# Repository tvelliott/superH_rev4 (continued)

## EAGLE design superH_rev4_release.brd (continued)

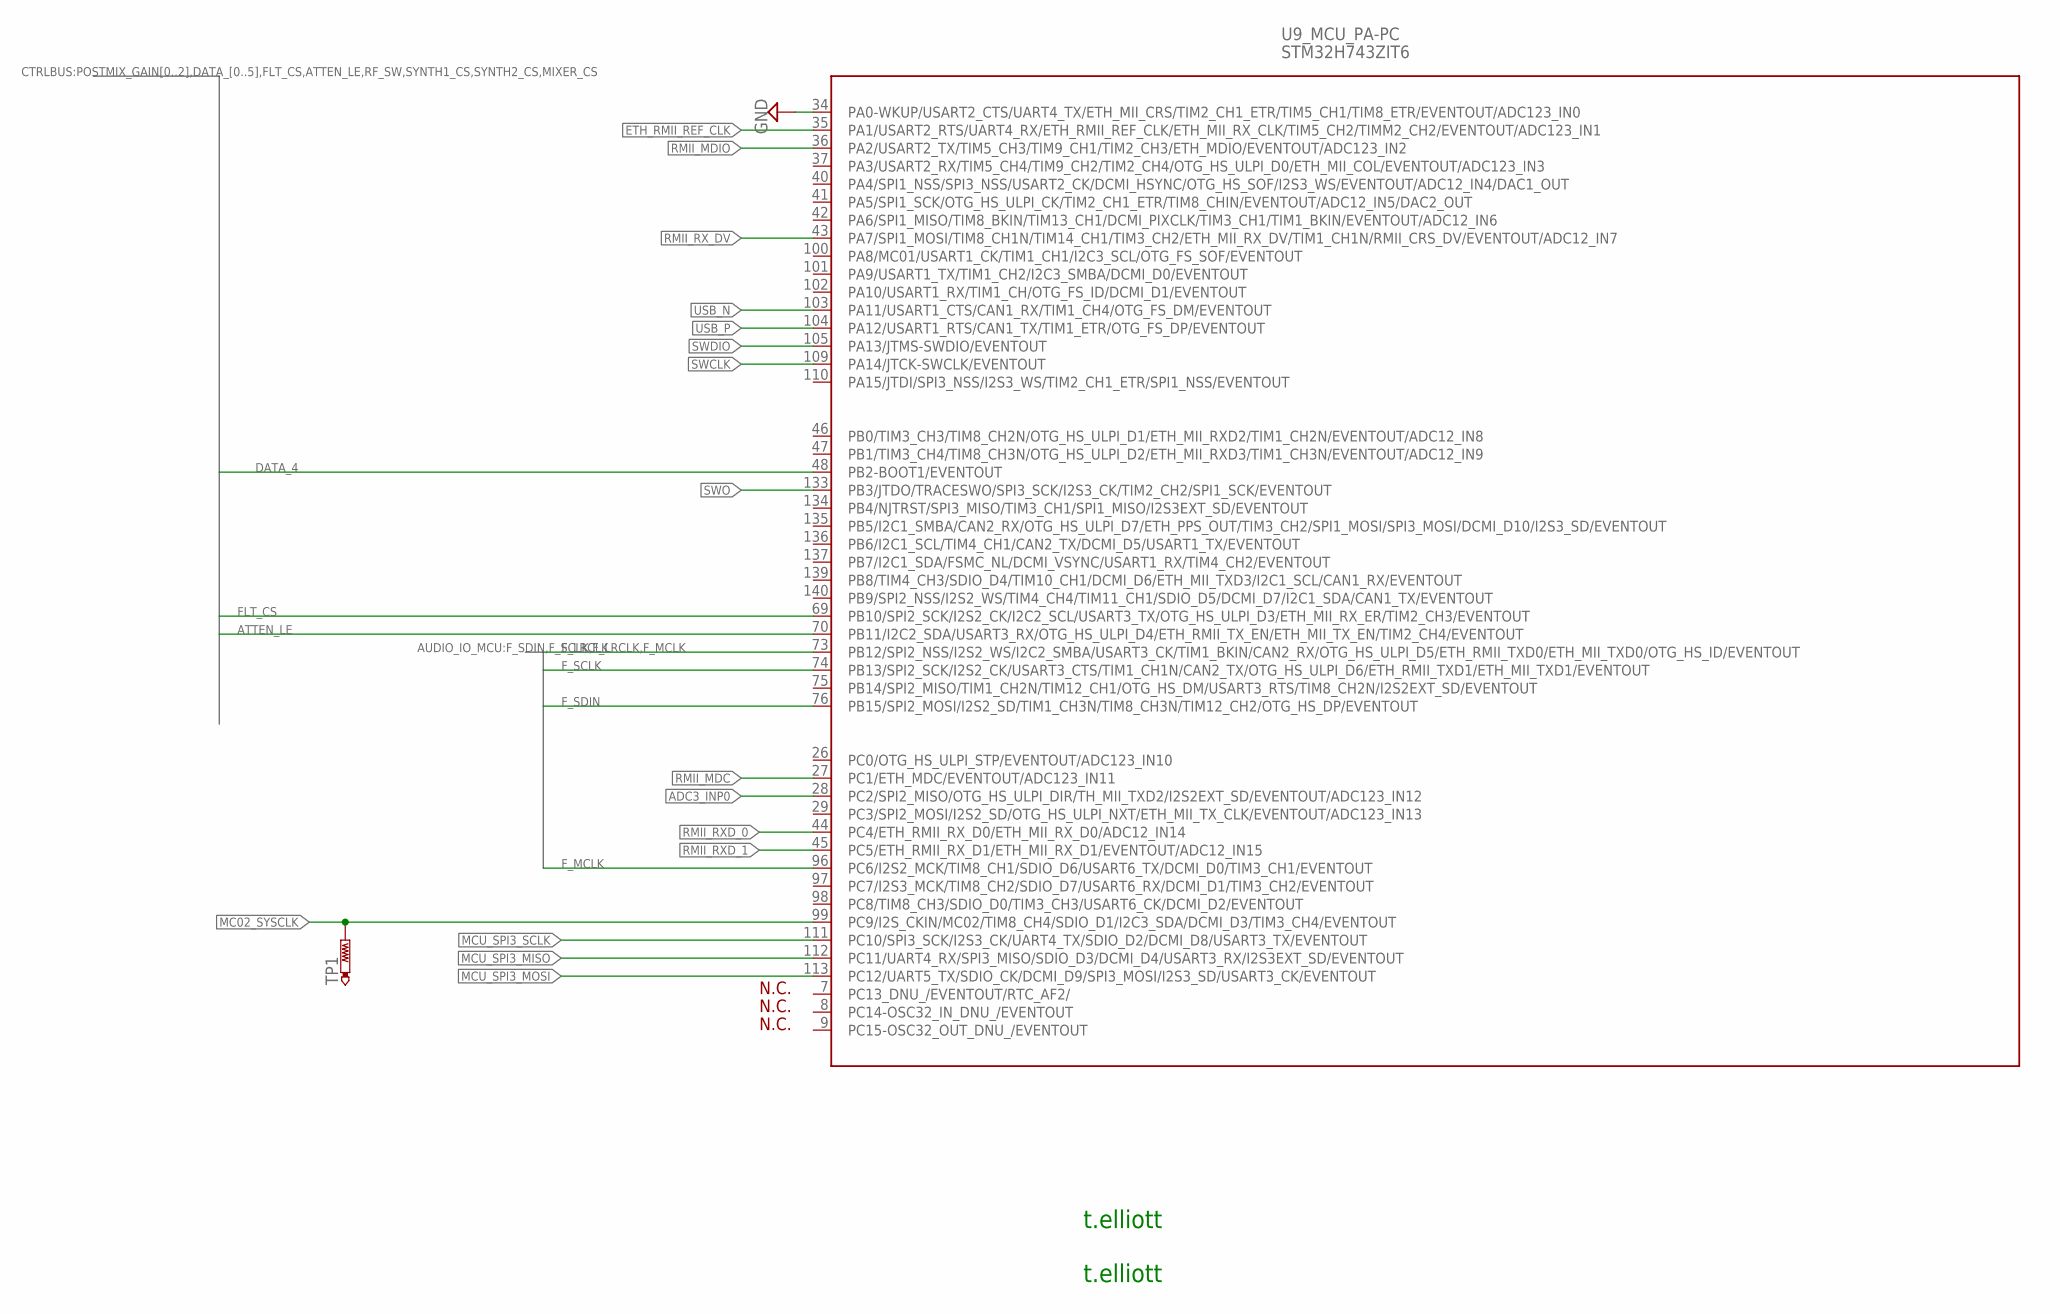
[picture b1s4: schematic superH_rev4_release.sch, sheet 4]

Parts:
TP1: PTR1TP08R; TP08R
U9: STM32H743ZIT6; STM32F407_144

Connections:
ADC3_INP0: U9.28 (PC2/SPI2_MISO/OTG_HS_ULPI_DIR/TH_MII_TX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); also elsewhere on the board
ATTEN_LE: U9.70 (PB11/I2C2_SDA/USART3_RX/OTG_HS_ULPI_D4/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); also elsewhere on the board
DATA_4: U9.48 (PB2-BOOT1/EVENTOUT); also elsewhere on the board
ETH_RMII_REF_CLK: U9.35 (PA1/USART2_RTS/UART4_RX/ETH_RMII_REF_CL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); also elsewhere on the board
FLT_CS: U9.69 (PB10/SPI2_SCK/I2S2_CK/I2C2_SCL/USART3_T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); also elsewhere on the board
F_LRCLK: U9.73 (PB12/SPI2_NSS/I2S2_WS/I2C2_SMBA/USART3_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); also elsewhere on the board
F_MCLK: U9.96 (PC6/I2S2_MCK/TIM8_CH1/SDIO_D6/USART6_TX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); also elsewhere on the board
F_SCLK: U9.74 (PB13/SPI2_SCK/I2S2_CK/USART3_CTS/TIM1_C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); also elsewhere on the board
F_SDIN: U9.76 (PB15/SPI2_MOSI/I2S2_SD/TIM1_CH3N/TIM8_C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); also elsewhere on the board
GND: U9.34 (PA0-WKUP/USART2_CTS/UART4_TX/ETH_MII_CR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); also elsewhere on the board
MC02_SYSCLK: TP1.TP, U9.99 (PC9/I2S_CKIN/MC02/TIM8_CH4/SDIO_D1/I2C3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)
MCU_SPI3_MISO: U9.112 (PC11/UART4_RX/SPI3_MISO/SDIO_D3/DCMI_D4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); also elsewhere on the board
MCU_SPI3_MOSI: U9.113 (PC12/UART5_TX/SDIO_CK/DCMI_D9/SPI3_MOSI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); also elsewhere on the board
MCU_SPI3_SCLK: U9.111 (PC10/SPI3_SCK/I2S3_CK/UART4_TX/SDIO_D2/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); also elsewhere on the board
RMII_MDC: U9.27 (PC1/ETH_MDC/EVENTOUT/ADC123_IN11); also elsewhere on the board
RMII_MDIO: U9.36 (PA2/USART2_TX/TIM5_CH3/TIM9_CH1/TIM2_CH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); also elsewhere on the board
RMII_RXD_0: U9.44 (PC4/ETH_RMII_RX_D0/ETH_MII_RX_D0/ADC12_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); also elsewhere on the board
RMII_RXD_1: U9.45 (PC5/ETH_RMII_RX_D1/ETH_MII_RX_D1/EVENTO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); also elsewhere on the board
RMII_RX_DV: U9.43 (PA7/SPI1_MOSI/TIM8_CH1N/TIM14_CH1/TIM3_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); also elsewhere on the board
SWCLK: U9.109 (PA14/JTCK-SWCLK/EVENTOUT); also elsewhere on the board
SWDIO: U9.105 (PA13/JTMS-SWDIO/EVENTOUT); also elsewhere on the board
SWO: U9.133 (PB3/JTDO/TRACESWO/SPI3_SCK/I2S3_CK/TIM2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); also elsewhere on the board
USB_N: U9.103 (PA11/USART1_CTS/CAN1_RX/TIM1_CH4/OTG_FS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); also elsewhere on the board
USB_P: U9.104 (PA12/USART1_RTS/CAN1_TX/TIM1_ETR/OTG_FS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); also elsewhere on the board

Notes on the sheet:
t.elliott

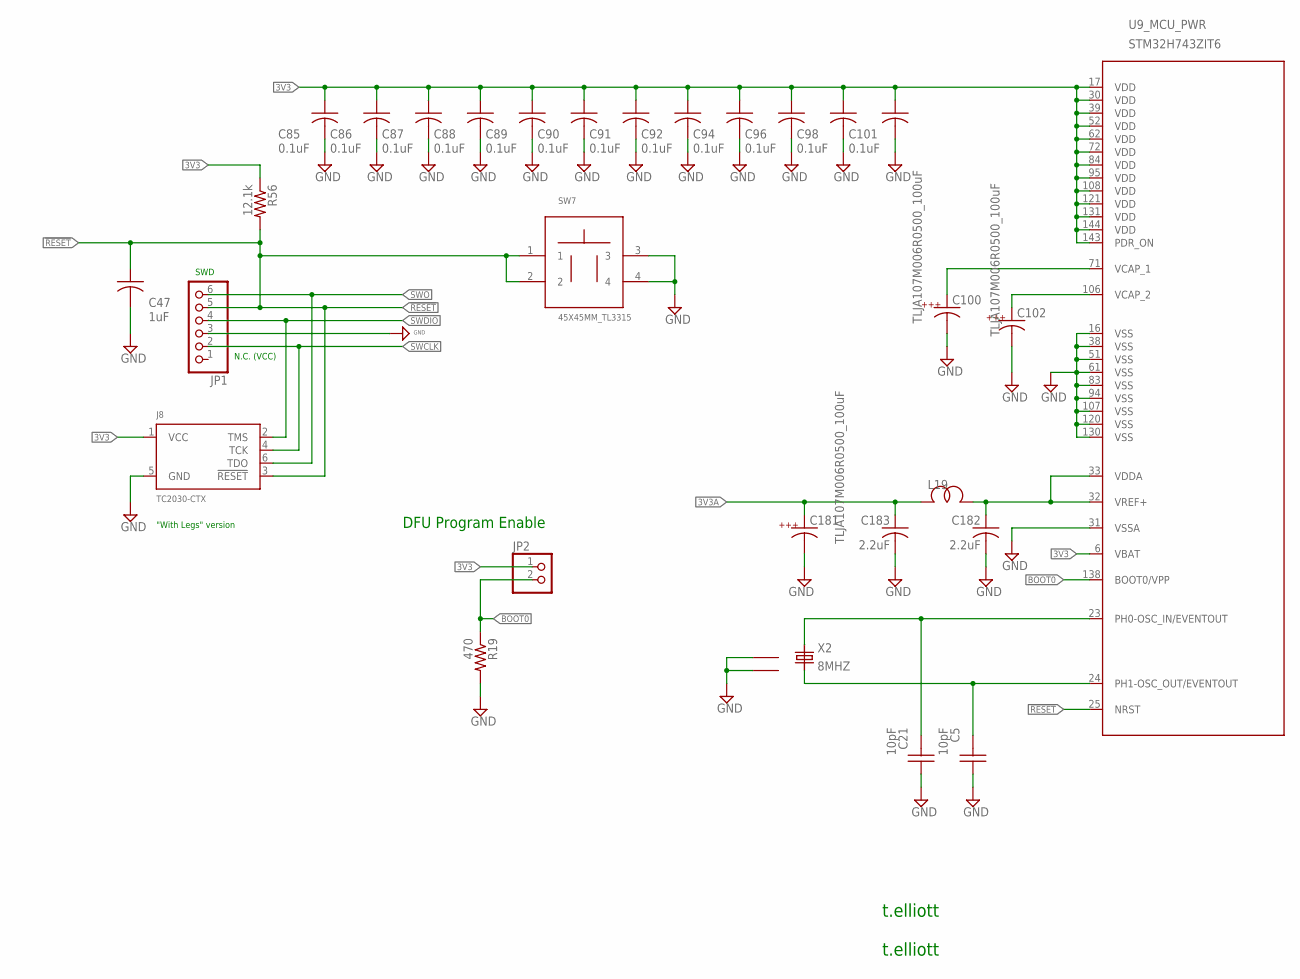
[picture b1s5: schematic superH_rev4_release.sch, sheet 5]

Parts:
C5, C21: 10pF; C0402
C47: 1uF; 0402
C85, C86, C87, C88, C89, C90, C91, C92, C94, C96, C98, C101: 0.1uF; 0402
C100, C102, C181: TLJA107M006R0500_100uF; 1210K
C182, C183: 2.2uF; C0805
J8: TC2030-CTX; TC2030-IDC
JP1: PINHD-1X6; 1X06
JP2: PINHD-1X2; 1X02
L19: WE-CBF_0603; 0603
R19: 470; R0402
R56: 12.1k; R0603
SW7: 45X45MM_TL3315; PBUT_SW_TACTILE_4_5MMX4_5MM
U9: STM32H743ZIT6; STM32F407_144
X2: 8MHZ; ECS-250-20-30B-DU_CRYSTAL

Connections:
3V3: C85.1 (A), C86.1 (A), C87.1 (A), C88.1 (A), C89.1 (A), C90.1 (A), C91.1 (A), C92.1 (A), C94.1 (A), C96.1 (A), C98.1 (A), C101.1 (A), J8.1 (VCC), JP2.1, R56.1, U9.6 (VBAT), U9.17 (VDD), U9.30 (VDD), U9.39 (VDD), U9.52 (VDD), U9.62 (VDD), U9.72 (VDD), U9.84 (VDD), U9.95 (VDD), U9.108 (VDD), U9.121 (VDD), U9.131 (VDD), U9.143 (PDR_ON), U9.144 (VDD); also elsewhere on the board
3V3A: C181.A, C183.1, L19.1; also elsewhere on the board
20MHZ_REF: C21.2, U9.23 (PH0-OSC_IN/EVENTOUT), X2.1
!RESET: C47.1 (A), J8.3 (!RESET), JP1.5, R56.2, SW7.1, SW7.2, U9.25 (NRST); also elsewhere on the board
BOOT0: JP2.2, R19.1, U9.138 (BOOT0/VPP)
GND: C5.1, C21.1, C47.2 (C), C85.2 (C), C86.2 (C), C87.2 (C), C88.2 (C), C89.2 (C), C90.2 (C), C91.2 (C), C92.2 (C), C94.2 (C), C96.2 (C), C98.2 (C), C100.C, C101.2 (C), C102.C, C181.C, C182.2, C183.2, J8.5 (GND), JP1.3, R19.2, SW7.3, SW7.4, U9.16 (VSS), U9.31 (VSSA), U9.38 (VSS), U9.51 (VSS), U9.61 (VSS), U9.83 (VSS), U9.94 (VSS), U9.107 (VSS), U9.120 (VSS), U9.130 (VSS), X2.GND@1 (1), X2.GND@2 (2); also elsewhere on the board
unnamed: C182.1, L19.2, U9.32 (VREF+), U9.33 (VDDA)
unnamed: C102.A, U9.106 (VCAP_2)
unnamed: C100.A, U9.71 (VCAP_1)
SWCLK: J8.4 (TCK), JP1.2; also elsewhere on the board
SWDIO: J8.2 (TMS), JP1.4; also elsewhere on the board
SWO: J8.6 (TDO), JP1.6; also elsewhere on the board
X2: C5.2, U9.24 (PH1-OSC_OUT/EVENTOUT), X2.3

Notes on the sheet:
t.elliott
SWD
N.C. (VCC)
"With Legs" version
DFU Program Enable

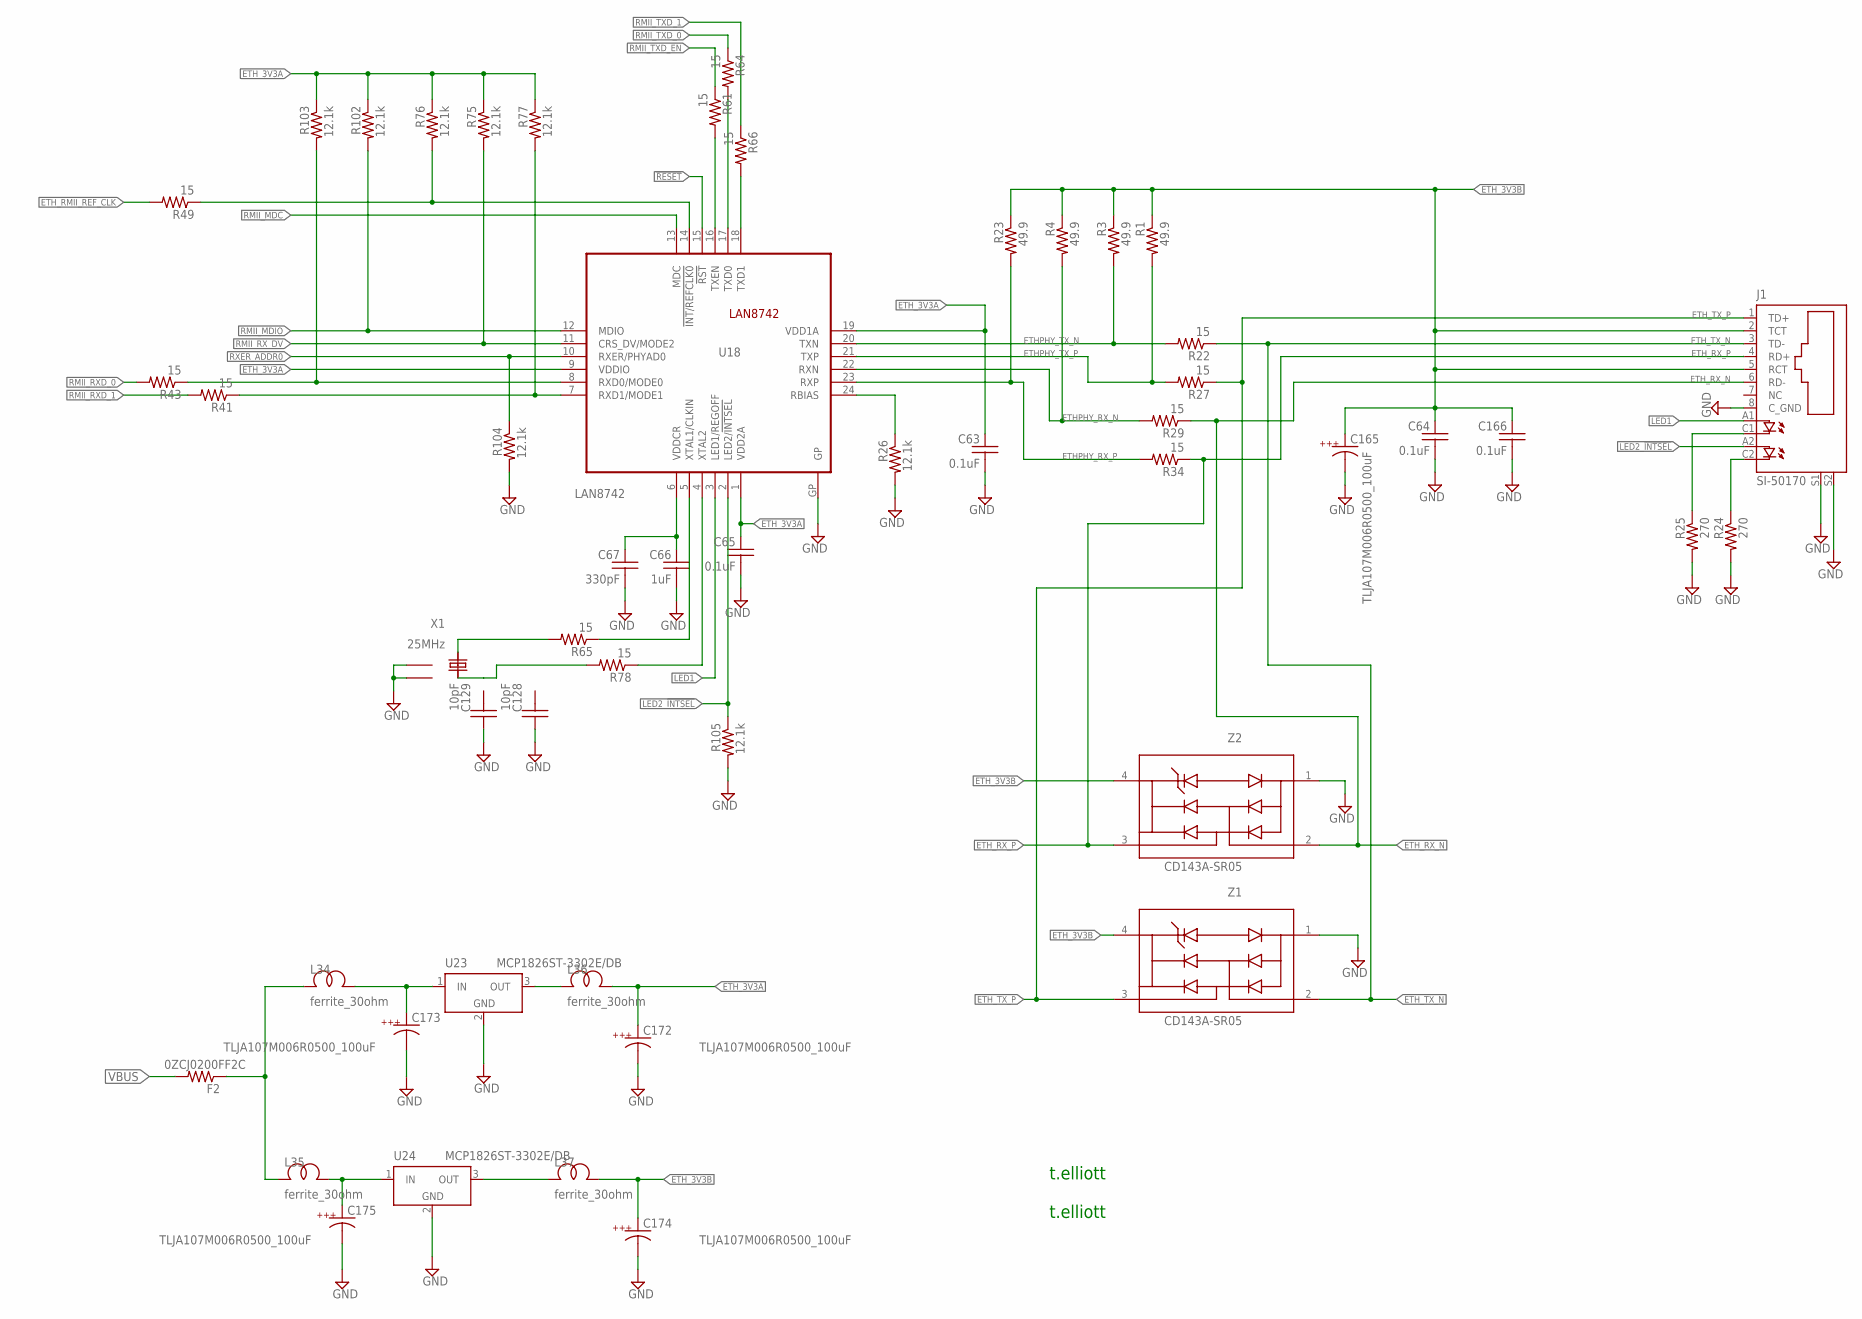
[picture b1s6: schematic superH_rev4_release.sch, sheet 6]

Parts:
C63, C64, C65, C166: 0.1uF; C0603
C66: 1uF; C0603
C67: 330pF; C0603
C128, C129: 10pF; C0402
C165, C172, C173, C174, C175: TLJA107M006R0500_100uF; 1210K
F2: 0ZCJ0200FF2C; R1206
J1: SI-50170
L34, L35, L36, L37: ferrite_30ohm; 0603
R1, R3, R4, R23: 49.9; R0603
R22, R27, R29, R34, R41, R43, R49, R61, R64, R65, R66, R78: 15; R0402
R24, R25: 270; R0603
R26, R75, R76, R77, R102, R103, R104, R105: 12.1k; R0603
U18: LAN8742; QFN-24
U23, U24: MCP1826ST-3302E/DB; SOT223
X1: 25MHz; ECS-250-20-30B-DU_CRYSTAL
Z1, Z2: CD143A-SR05; SR2.8.TCT_1PRIMARY

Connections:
!RESET: U18.15 (!RST); also elsewhere on the board
ETHPHY_RX_N: R4.2, R29.2, U18.22 (RXN)
ETHPHY_RX_P: R23.2, R34.2, U18.23 (RXP)
ETHPHY_TX_N: R3.2, R22.2, U18.20 (TXN)
ETHPHY_TX_P: R1.2, R27.2, U18.21 (TXP)
ETH_3V3A: C63.1, C65.1, C172.A, L36.2, R75.1, R76.1, R77.1, R102.1, R103.1, U18.1 (VDD2A), U18.9 (VDDIO), U18.19 (VDD1A)
ETH_3V3B: C64.1, C165.A, C166.1, C174.A, J1.2 (TCT), J1.5 (RCT), L37.2, R1.1, R3.1, R4.1, R23.1, Z1.4 (REF), Z2.4 (REF)
ETH_RMII_REF_CLK: R49.2; also elsewhere on the board
ETH_RX_N: J1.6 (RD-), R29.1, Z2.2 (I/O)
ETH_RX_P: J1.4 (RD+), R34.1, Z2.3 (I/O)
ETH_TX_N: J1.3 (TD-), R22.1, Z1.2 (I/O)
ETH_TX_P: J1.1 (TD+), R27.1, Z1.3 (I/O)
ETH_VIN: F2.1, L34.1, L35.1
GND: C63.2, C64.2, C65.2, C66.2, C67.2, C128.1, C129.1, C165.C, C166.2, C172.C, C173.C, C174.C, C175.C, J1.8 (C_GND), J1.S1, J1.S2, R24.2, R25.2, R26.2, R104.2, R105.2, U18.GP, U23.2 (GND), U23.4 (GND), U24.2 (GND), U24.4 (GND), X1.GND@1 (1), X1.GND@2 (2), Z1.1 (GND), Z2.1 (GND); also elsewhere on the board
LED1: J1.A1 (A), U18.3 (LED1/REGOFF)
LED2_!INTSEL: J1.A2 (A1), R105.1, U18.2 (LED2/!INTSEL)
unnamed: C173.A, L34.2, U23.1 (IN)
unnamed: R26.1, U18.24 (RBIAS)
unnamed: C66.1, C67.1, U18.6 (VDDCR)
unnamed: J1.C2 (C1), R24.1
unnamed: J1.C1 (C), R25.1
unnamed: R78.1, U18.4 (XTAL2)
unnamed: R65.1, U18.5 (XTAL1/CLKIN)
unnamed: C175.A, L35.2, U24.1 (IN)
unnamed: L37.1, U24.3 (OUT)
unnamed: L36.1, U23.3 (OUT)
unnamed: R78.2, X1.3
unnamed: R65.2, X1.1
REF_CLK: R49.1, R76.2, U18.14 (!INT/REFCLK0)
RMII_MDC: U18.13 (MDC); also elsewhere on the board
RMII_MDIO: R102.2, U18.12 (MDIO); also elsewhere on the board
RMII_RXD_0: R43.2; also elsewhere on the board
RMII_RXD_1: R41.2; also elsewhere on the board
RMII_RX_DV: R75.2, U18.11 (CRS_DV/MODE2); also elsewhere on the board
RMII_TXD_0: R64.1; also elsewhere on the board
RMII_TXD_1: R66.1; also elsewhere on the board
RMII_TXD_EN: R61.1; also elsewhere on the board
RXD0: R43.1, R103.2, U18.8 (RXD0/MODE0)
RXD1: R41.1, R77.2, U18.7 (RXD1/MODE1)
RXER_ADDR0: R104.1, U18.10 (RXER/PHYAD0)
TXD0: R64.2, U18.17 (TXD0)
TXD1: R66.2, U18.18 (TXD1)
TXEN: R61.2, U18.16 (TXEN)
VBUS: F2.2; also elsewhere on the board

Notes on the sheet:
t.elliott

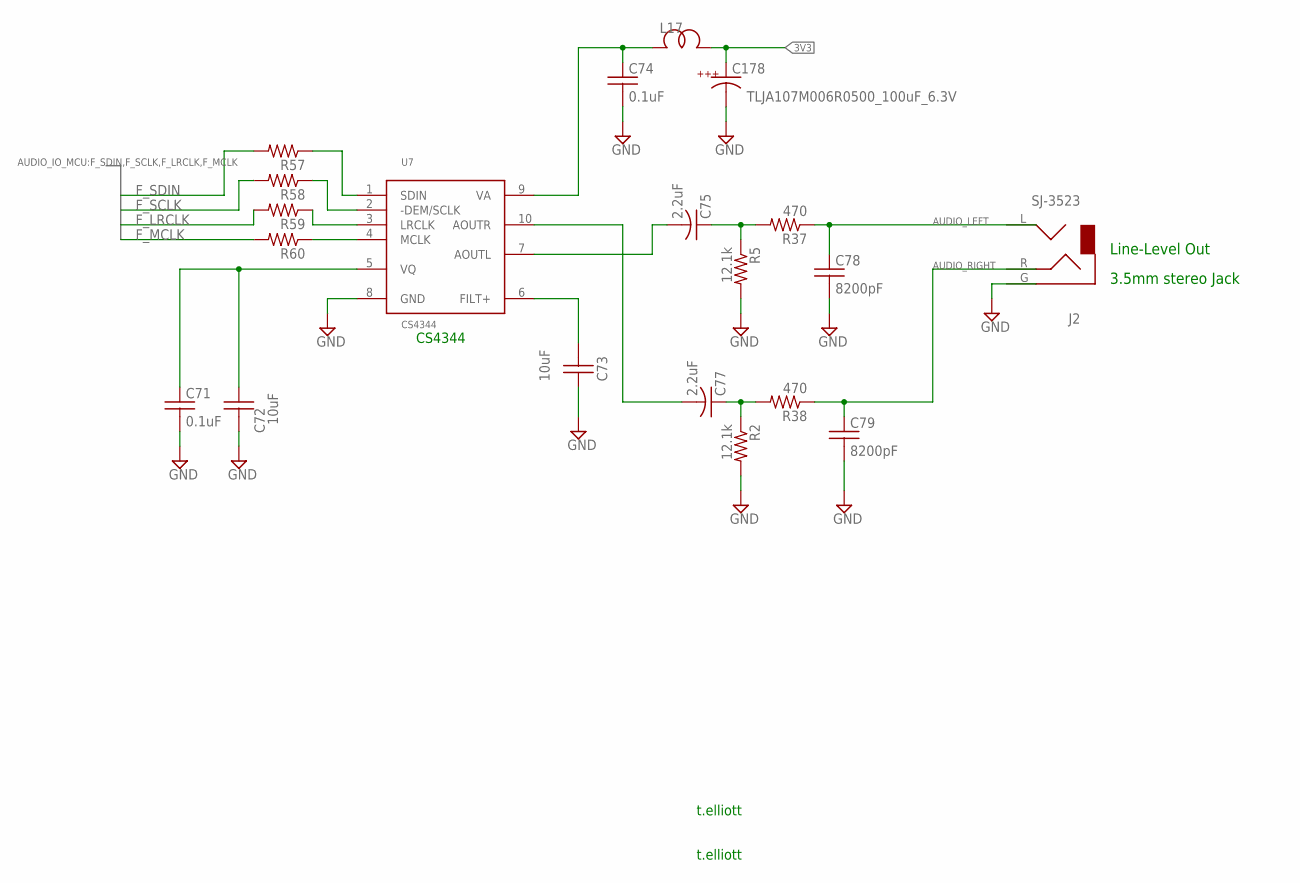
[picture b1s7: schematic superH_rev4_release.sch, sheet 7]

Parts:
C71, C74: 0.1uF; C0603
C72, C73: 10uF; C0805
C75, C77: 2.2uF; C0805
C78, C79: 8200pF; C0603
C178: TLJA107M006R0500_100uF_6.3V; 1210K
J2: SJ-3523
L17: WE-CBF_0603; 0603
R2, R5: 12.1k; R0603
R37, R38, R57, R58, R59, R60: 470; R0402
U7: CS4344; MSOP10

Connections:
3V3: C178.A, L17.2; also elsewhere on the board
AUDIO_LEFT: C79.1, J2.R, R38.1
AUDIO_RIGHT: C78.1, J2.L, R37.1
F_LRCLK: R59.2; also elsewhere on the board
F_MCLK: R60.2; also elsewhere on the board
F_SCLK: R58.2; also elsewhere on the board
F_SDIN: R57.2; also elsewhere on the board
GND: C71.2, C72.2, C73.1, C74.2, C78.2, C79.2, C178.C, J2.G, R2.2, R5.2, U7.8 (GND); also elsewhere on the board
unnamed: C77.2, U7.10 (AOUTR)
unnamed: R60.1, U7.4 (MCLK)
unnamed: R59.1, U7.3 (LRCLK)
unnamed: R58.1, U7.2 (-DEM/SCLK)
unnamed: R57.1, U7.1 (SDIN)
unnamed: C73.2, U7.6 (FILT+)
unnamed: C71.1, C72.1, U7.5 (VQ)
unnamed: C75.2, U7.7 (AOUTL)
unnamed: C75.1, R5.1, R37.2
unnamed: C77.1, R2.1, R38.2
unnamed: C74.1, L17.1, U7.9 (VA)

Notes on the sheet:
t.elliott
CS4344
Line-Level Out
3.5mm stereo Jack

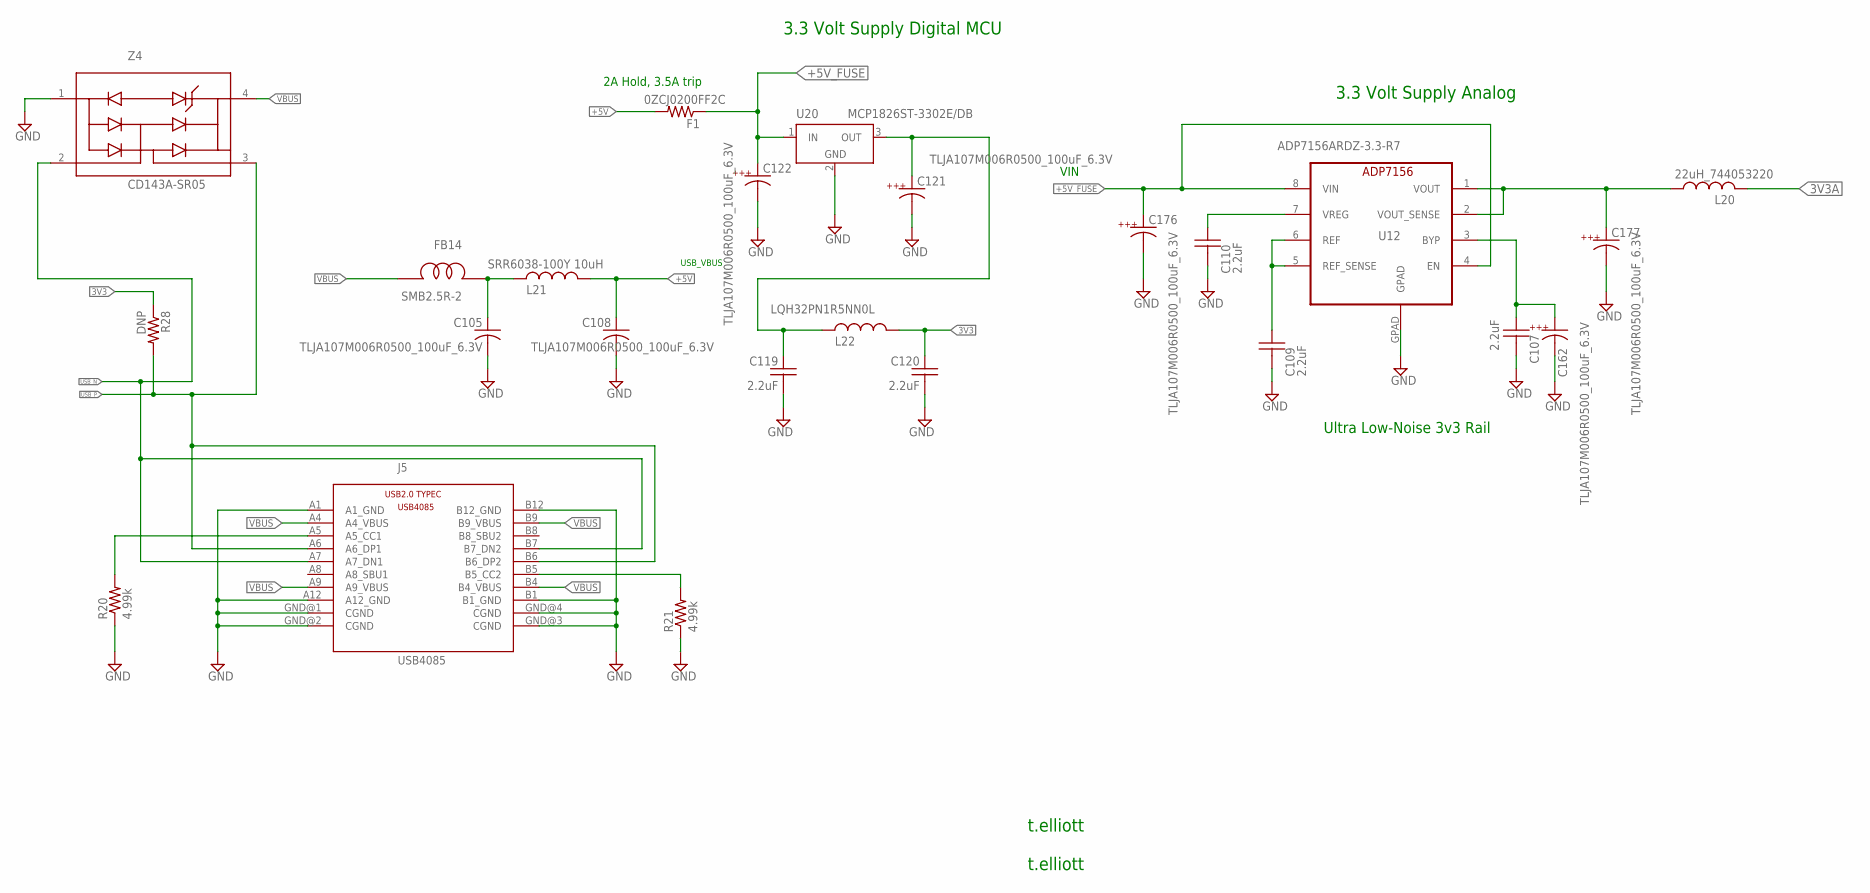
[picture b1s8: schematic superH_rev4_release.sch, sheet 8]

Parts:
C105, C108, C121, C122, C162, C176, C177: TLJA107M006R0500_100uF_6.3V; 1210K
C107, C109, C110: 2.2uF; C0805
C119, C120: 2.2uF; C0603
F1: 0ZCJ0200FF2C; R1206
FB14: SMB2.5R-2; SMB2.5-2
J5: USB4085; GCT_PN_USB4085
L20: 22uH_744053220; POWER-CHOKE_WE-TPC
L21: SRR6038-100Y 10uH; POWER-CHOKE_WE-TPC
L22: LQH32PN1R5NN0L; L3225M; PARTNUMBER ELJ-PA331KF
R20, R21: 4.99k; R0402
R28: DNP; R0603
U12: ADP7156ARDZ-3.3-R7; SO8
U20: MCP1826ST-3302E/DB; SOT223
Z4: CD143A-SR05; SR2.8.TCT_1PRIMARY

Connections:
3V3: C120.1, L22.1, R28.1; also elsewhere on the board
3V3A: L20.2; also elsewhere on the board
3V3_VIN: C119.1, C121.A, L22.2, U20.3 (OUT)
+5V: C108.A, F1.2, L21.1
+5V_FUSE: C122.A, C176.A, F1.1, U12.4 (EN), U12.8 (VIN), U20.1 (IN); also elsewhere on the board
GND: C105.C, C107.2, C108.C, C109.2, C110.2, C119.2, C120.2, C121.C, C122.C, C162.C, C176.C, C177.C, J5.A1 (A1_GND), J5.A12 (A12_GND), J5.B1 (B1_GND), J5.B12 (B12_GND), J5.GND@1 (CGND), J5.GND@2 (CGND), J5.GND@3 (CGND), J5.GND@4 (CGND), R20.1, R21.1, U12.GPAD, U20.2 (GND), U20.4 (GND), Z4.1 (GND); also elsewhere on the board
unnamed: J5.B5 (B5_CC2), R21.2
unnamed: C177.A, L20.1, U12.1 (VOUT), U12.2 (VOUT_SENSE)
unnamed: C109.1, U12.5 (REF_SENSE), U12.6 (REF)
unnamed: C110.1, U12.7 (VREG)
unnamed: C107.1, C162.A, U12.3 (BYP)
unnamed: C105.A, FB14.P$2, L21.2
unnamed: J5.A5 (A5_CC1), R20.2
USB_N: J5.A7 (A7_DN1), J5.B7 (B7_DN2), Z4.2 (I/O); also elsewhere on the board
USB_P: J5.A6 (A6_DP1), J5.B6 (B6_DP2), R28.2, Z4.3 (I/O); also elsewhere on the board
VBUS: FB14.P$1, J5.A4 (A4_VBUS), J5.A9 (A9_VBUS), J5.B4 (B4_VBUS), J5.B9 (B9_VBUS), Z4.4 (REF); also elsewhere on the board

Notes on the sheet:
t.elliott
VIN
3.3 Volt Supply Digital MCU
USB_VBUS
Ultra Low-Noise 3v3 Rail
2A Hold, 3.5A trip
3.3 Volt Supply Analog

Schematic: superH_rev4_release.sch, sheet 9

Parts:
FAB1, FAB2, FAB3, FAB4, FAB5, FAB6: 2118724; RF_SHIELD
FID1, FID2, FID3, FID4: FIDUCIALSMD; FIDUCIAL
H1, H2, H3, H4, H5, H6: MOUNT-PAD-ROUND2.8; 2,8-PAD

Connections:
GND: FAB1.P$1, FAB1.P$2, FAB1.P$3, FAB1.P$4, FAB1.P$5, FAB1.P$6, FAB1.P$7, FAB1.P$8, FAB1.P$9, FAB1.P$10, FAB1.P$11, FAB1.P$12, FAB1.P$13, FAB1.P$14, FAB1.P$15, FAB1.P$16, FAB1.P$17, FAB1.P$18, FAB1.P$19, FAB1.P$20, FAB1.P$21, FAB1.P$22, FAB1.P$23, FAB1.P$24, FAB2.P$1, FAB2.P$2, FAB2.P$3, FAB2.P$4, FAB2.P$5, FAB2.P$6, FAB2.P$7, FAB2.P$8, FAB2.P$9, FAB2.P$10, FAB2.P$11, FAB2.P$12, FAB2.P$13, FAB2.P$14, FAB2.P$15, FAB2.P$16, FAB2.P$17, FAB2.P$18, FAB2.P$19, FAB2.P$20, FAB2.P$21, FAB2.P$22, FAB2.P$23, FAB2.P$24, FAB3.P$1, FAB3.P$2, FAB3.P$3, FAB3.P$4, FAB3.P$5, FAB3.P$6, FAB3.P$7, FAB3.P$8, FAB3.P$9, FAB3.P$10, FAB3.P$11, FAB3.P$12, FAB3.P$13, FAB3.P$14, FAB3.P$15, FAB3.P$16, FAB3.P$17, FAB3.P$18, FAB3.P$19, FAB3.P$20, FAB3.P$21, FAB3.P$22, FAB3.P$23, FAB3.P$24, FAB4.P$1, FAB4.P$2, FAB4.P$3, FAB4.P$4, FAB4.P$5, FAB4.P$6, FAB4.P$7, FAB4.P$8, FAB4.P$9, FAB4.P$10, FAB4.P$11, FAB4.P$12, FAB4.P$13, FAB4.P$14, FAB4.P$15, FAB4.P$16, FAB4.P$17, FAB4.P$18, FAB4.P$19, FAB4.P$20, FAB4.P$21, FAB4.P$22, FAB4.P$23, FAB4.P$24, FAB5.P$1, FAB5.P$2, FAB5.P$3, FAB5.P$4, FAB5.P$5, FAB5.P$6, FAB5.P$7, FAB5.P$8, FAB5.P$9, FAB5.P$10, FAB5.P$11, FAB5.P$12, FAB5.P$13, FAB5.P$14, FAB5.P$15, FAB5.P$16, FAB5.P$17, FAB5.P$18, FAB5.P$19, FAB5.P$20, FAB5.P$21, FAB5.P$22, FAB5.P$23, FAB5.P$24, FAB6.P$1, FAB6.P$2, FAB6.P$3, FAB6.P$4, FAB6.P$5, FAB6.P$6, FAB6.P$7, FAB6.P$8, FAB6.P$9, FAB6.P$10, FAB6.P$11, FAB6.P$12, FAB6.P$13, FAB6.P$14, FAB6.P$15, FAB6.P$16, FAB6.P$17, FAB6.P$18, FAB6.P$19, FAB6.P$20, FAB6.P$21, FAB6.P$22, FAB6.P$23, FAB6.P$24; also elsewhere on the board

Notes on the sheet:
t.elliott

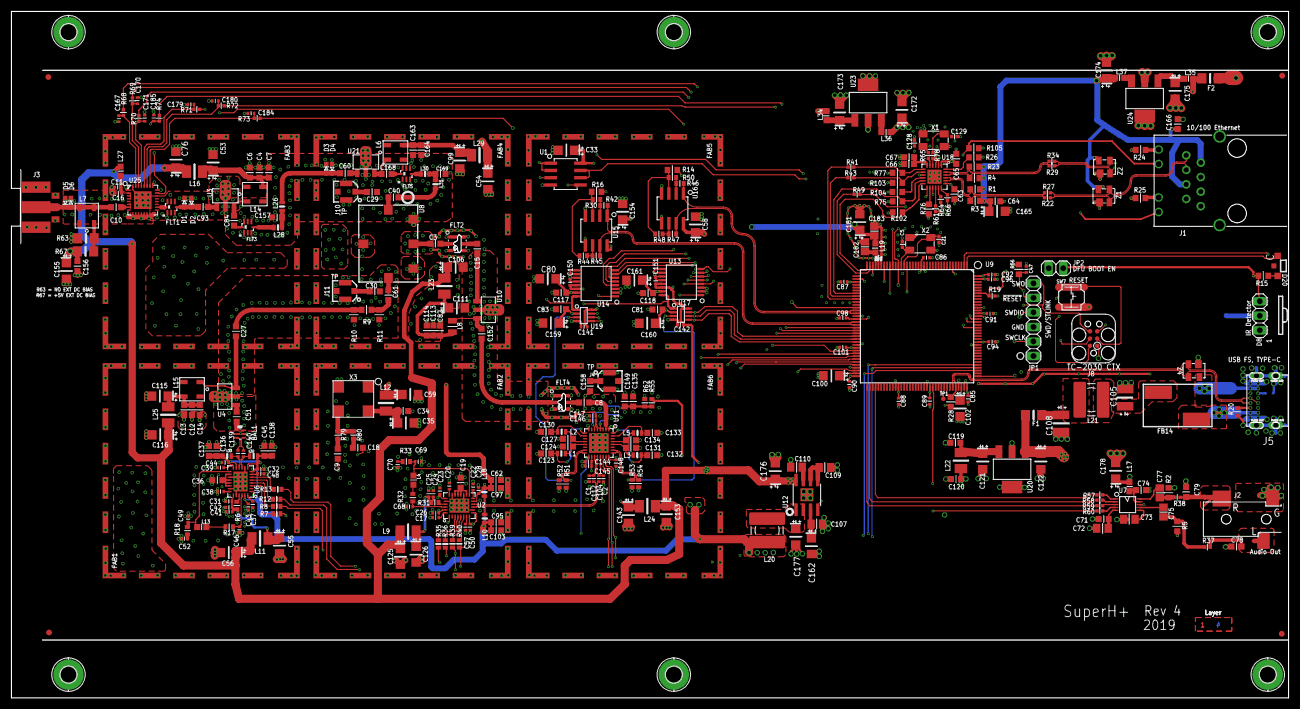
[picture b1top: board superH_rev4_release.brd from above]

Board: 4 copper layers, 223.3 x 120.0 mm, 380 parts (1 on the bottom side), 228 nets.

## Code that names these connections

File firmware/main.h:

//MIT License
//
//Copyright (c) 2019 tvelliott
//
//Permission is hereby granted, free of charge, to any person obtaining a copy
//of this software and associated documentation files (the "Software"), to deal
//in the Software without restriction, including without limitation the rights
//to use, copy, modify, merge, publish, distribute, sublicense, and/or sell
//copies of the Software, and to permit persons to whom the Software is
//furnished to do so, subject to the following conditions:
//
//The above copyright notice and this permission notice shall be included in all
//copies or substantial portions of the Software.
//
//THE SOFTWARE IS PROVIDED "AS IS", WITHOUT WARRANTY OF ANY KIND, EXPRESS OR
//IMPLIED, INCLUDING BUT NOT LIMITED TO THE WARRANTIES OF MERCHANTABILITY,
//FITNESS FOR A PARTICULAR PURPOSE AND NONINFRINGEMENT. IN NO EVENT SHALL THE
//AUTHORS OR COPYRIGHT HOLDERS BE LIABLE FOR ANY CLAIM, DAMAGES OR OTHER
//LIABILITY, WHETHER IN AN ACTION OF CONTRACT, TORT OR OTHERWISE, ARISING FROM,
//OUT OF OR IN CONNECTION WITH THE SOFTWARE OR THE USE OR OTHER DEALINGS IN THE
//SOFTWARE.



#ifndef __MAIN_H__
#define __MAIN_H__

#include "stm32h7xx_hal.h"

#define ARM_MATH_CM7 1
#include "arm_common_tables.h"
#include "arm_math.h"

#define IN_BUFFER_N 16
#define N_SAMPLES 256

extern volatile int do_sample_process;
extern volatile int rssi_offset;
extern volatile int bb_gain;
extern volatile int fft_buffer_ready;
extern volatile int adc_rate;
extern volatile int stats_buffer_ready;
extern volatile int channel_settle;
extern volatile int squelch_timer;
extern volatile double d_alpha_i;
extern volatile double d_alpha_q;
extern volatile double d_beta_i;
extern volatile double d_beta_q;
void reset_channel_timeout( void );
void set_channel_timeout_zero( void );
void set_channel_timeout_min( void );
void scanner_next_channel( void );
double get_current_freq( void );
void process_incoming_rf( void );
int upsample_audio( uint8_t *buffer, int len );
void _Error_Handler( char *file, int line );
void calc_stddev( int16_t *data, int n );
int main( void );
float atan2f( float y, float x );
float get_real_amp( void );
extern volatile int udp_out_len;
extern float eqlms_dhat[1];
extern float eqlms_d[1];
extern float eqlms_mu;
extern float eqlms_beta;
extern unsigned int eqlms_m;
extern unsigned int eqlms_k;
extern struct eqlms_rf_s *eqlms;
extern struct freqmod_s *freqmod;
extern struct nco_cf_s *nco;
extern volatile int upsample_ready;
extern volatile short upsampled[160 * 6];
extern struct resamp_rf_s *audio_resamp_q;
extern unsigned int audio_resamp_npfb;
extern float audio_resamp_bw;
extern float audio_resamp_As;
extern unsigned int audio_resamp_m;
extern float audio_resamp_r;
extern unsigned int ch_ny;
extern struct resamp2_s *halfband_q;
extern float half_band_as;
extern unsigned int half_band_m;
extern struct resamp_cf_s *ch_resamp_q;
extern unsigned int ch_resamp_npfb;
extern float ch_resamp_bw;
extern float ch_resamp_As;
extern unsigned int ch_resamp_m;
extern float ch_resamp_r;
extern struct symsync_s *q;
extern struct symsync_s symsync;
extern float symsync_buf_out[1];
extern float symsync_buf_in[1];
extern unsigned int symsync_npfb;
extern float symsync_beta;
extern unsigned int symsync_m;
extern unsigned int symsync_k;
extern int symsync_ftype;
extern unsigned int did_sym;
void tcp_iperf_init( void );
static void MX_SPI3_Init( void );
static void SystemClock_Config( void );
extern volatile int fm_cnt;
extern int eqlms_trained;
extern int do_silent_frame;
extern int audio_frames_done;
extern volatile struct udp_pcb *udp_data_pcb;
extern int64_t __errno;
extern volatile int scanner_mod;
extern volatile int in_buffer_len;
extern volatile char in_buffer_tmp[1500 * IN_BUFFER_N];
extern volatile char in_buffer[1500 * IN_BUFFER_N];
extern int found_signal;
extern volatile int sample_cnt;
extern volatile uint32_t uptime_sec;
extern volatile uint32_t second_tick;
void main_tick( void );
void main_tick();
void led_tick( void );
void led_tick();
int _mem_free( void );
void udp_data_rx( void *arg, struct udp_pcb *pcb, struct pbuf *p, struct ip4_addr *addr, uint16_t port );
void p25_udp_init( void );
void p25_udp_init();
void udp_send_data( uint8_t *buffer, int len );
void udp_send_data( uint8_t *buffer, int len );
void process_incoming_samples( int16_t val );
void process_incoming_samples( int16_t val );
void p25_net_tick( void );
extern SPI_HandleTypeDef hspi3;
extern ADC_HandleTypeDef hadc3;
extern ADC_HandleTypeDef hadc2;
extern ADC_HandleTypeDef hadc1;
extern volatile int did_print_channel;
extern volatile double scanner_freq_p25[];
extern volatile int scanner_channel_mask[];
extern volatile int scanner_freqs;
extern volatile int8_t std_dev;
extern volatile uint32_t scanner_idle_time;
extern volatile int scanner_channel;
extern volatile int channel_timeout;
extern int stddev_n;
extern float32_t stddev_out;
extern float32_t stddev_in[N_SAMPLES];
extern volatile int do_low_if_mix;
extern volatile int do_48khz_iq_only;
extern volatile int do_freq_offset;
extern volatile struct ip4_addr udp_saddr;

#define LED1_Pin GPIO_PIN_2
#define LED1_GPIO_Port GPIOE
#define LED2_Pin GPIO_PIN_4 //actually 3
#define LED2_GPIO_Port GPIOE
#define data_4_Pin GPIO_PIN_2
#define data_4_GPIO_Port GPIOB
#define data_0_Pin GPIO_PIN_15
#define data_0_GPIO_Port GPIOF
#define data_1_Pin GPIO_PIN_0
#define data_1_GPIO_Port GPIOG
#define data_2_Pin GPIO_PIN_1
#define data_2_GPIO_Port GPIOG
#define postmix_gain2_Pin GPIO_PIN_7
#define postmix_gain2_GPIO_Port GPIOE
#define postmix_gain1_Pin GPIO_PIN_8
#define postmix_gain1_GPIO_Port GPIOE
#define postmix_gain0_Pin GPIO_PIN_9
#define postmix_gain0_GPIO_Port GPIOE
#define data_3_Pin GPIO_PIN_10
#define data_3_GPIO_Port GPIOE
#define data_5_Pin GPIO_PIN_11
#define data_5_GPIO_Port GPIOE
#define rf_sw_Pin GPIO_PIN_12
#define rf_sw_GPIO_Port GPIOE
#define mixer_cs_Pin GPIO_PIN_13
#define mixer_cs_GPIO_Port GPIOE
#define synth1_cs_Pin GPIO_PIN_14
#define synth1_cs_GPIO_Port GPIOE
#define synth2_cs_Pin GPIO_PIN_15
#define synth2_cs_GPIO_Port GPIOE
#define FLT_CS_Pin GPIO_PIN_10
#define FLT_CS_GPIO_Port GPIOB
#define atten_le_Pin GPIO_PIN_11
#define atten_le_GPIO_Port GPIOB
#define IR_INPUT_Pin GPIO_PIN_3
#define IR_INPUT_GPIO_Port GPIOE

#endif

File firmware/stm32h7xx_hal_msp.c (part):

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
    __HAL_RCC_GPIOF_CLK_ENABLE();
    /**ADC1 GPIO Configuration
    PF11     ------> ADC1_INP2
    PF12     ------> ADC1_INN2
    */
    GPIO_InitStruct.Pin = GPIO_PIN_11 | GPIO_PIN_12;
    GPIO_InitStruct.Mode = GPIO_MODE_ANALOG;
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    __HAL_RCC_GPIOF_CLK_ENABLE();
    __HAL_RCC_GPIOC_CLK_ENABLE();
    /**ADC3 GPIO Configuration
    PF10     ------> ADC3_INP6
    PC2_C     ------> ADC3_INN1
    PC2_C     ------> ADC3_INP0
    */
    GPIO_InitStruct.Pin = GPIO_PIN_10;
    GPIO_InitStruct.Mode = GPIO_MODE_ANALOG;
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    }

    /**ADC1 GPIO Configuration
    PF11     ------> ADC1_INP2
    PF12     ------> ADC1_INN2
    */
    HAL_GPIO_DeInit( GPIOF, GPIO_PIN_11 | GPIO_PIN_12 );

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    }

    /**ADC2 GPIO Configuration
    PF13     ------> ADC2_INP2
    PF14     ------> ADC2_INN2
    */
    HAL_GPIO_DeInit( GPIOF, GPIO_PIN_13 | GPIO_PIN_14 );

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    __HAL_RCC_ADC3_CLK_DISABLE();

    /**ADC3 GPIO Configuration
    PF10     ------> ADC3_INP6
    PC2_C     ------> ADC3_INN1
    PC2_C     ------> ADC3_INP0
    */
    HAL_GPIO_DeInit( GPIOF, GPIO_PIN_10 );

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    __HAL_RCC_GPIOB_CLK_ENABLE();
    __HAL_RCC_GPIOC_CLK_ENABLE();
    /**I2S2 GPIO Configuration
    PB12     ------> I2S2_WS
    PB13     ------> I2S2_CK
    PB15     ------> I2S2_SDO
    PC6     ------> I2S2_MCK
    */
    GPIO_InitStruct.Pin = GPIO_PIN_12 | GPIO_PIN_13 | GPIO_PIN_15;
    GPIO_InitStruct.Mode = GPIO_MODE_AF_PP;
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    __HAL_RCC_SPI2_CLK_DISABLE();

    /**I2S2 GPIO Configuration
    PB12     ------> I2S2_WS
    PB13     ------> I2S2_CK
    PB15     ------> I2S2_SDO
    PC6     ------> I2S2_MCK
    */
    HAL_GPIO_DeInit( GPIOB, GPIO_PIN_12 | GPIO_PIN_13 | GPIO_PIN_15 );

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
    __HAL_RCC_GPIOC_CLK_ENABLE();
    /**SPI3 GPIO Configuration
    PC10     ------> SPI3_SCK
    PC11     ------> SPI3_MISO
    PC12     ------> SPI3_MOSI
    */
    GPIO_InitStruct.Pin = GPIO_PIN_10 | GPIO_PIN_11 | GPIO_PIN_12;
    GPIO_InitStruct.Mode = GPIO_MODE_AF_PP;
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    __HAL_RCC_SPI3_CLK_DISABLE();

    /**SPI3 GPIO Configuration
    PC10     ------> SPI3_SCK
    PC11     ------> SPI3_MISO
    PC12     ------> SPI3_MOSI
    */
    HAL_GPIO_DeInit( GPIOC, GPIO_PIN_10 | GPIO_PIN_11 | GPIO_PIN_12 );

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
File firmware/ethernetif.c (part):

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    __HAL_RCC_ETH1RX_CLK_ENABLE();

    /**ETH GPIO Configuration
    PC1     ------> ETH_MDC
    PA1     ------> ETH_REF_CLK
    PA2     ------> ETH_MDIO
    PA7     ------> ETH_CRS_DV
    PC4     ------> ETH_RXD0
    PC5     ------> ETH_RXD1
    PG14     ------> ETH_TXD1
    PG11     ------> ETH_TX_EN
    PG13     ------> ETH_TXD0
    */
    GPIO_InitStruct.Pin = GPIO_PIN_1 | GPIO_PIN_4 | GPIO_PIN_5;
    GPIO_InitStruct.Mode = GPIO_MODE_AF_PP;
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    __HAL_RCC_ETH1RX_CLK_DISABLE();

    /**ETH GPIO Configuration
    PC1     ------> ETH_MDC
    PA1     ------> ETH_REF_CLK
    PA2     ------> ETH_MDIO
    PA7     ------> ETH_CRS_DV
    PC4     ------> ETH_RXD0
    PC5     ------> ETH_RXD1
    PG14     ------> ETH_TXD1
    PG11     ------> ETH_TX_EN
    PG13     ------> ETH_TXD0
    */
    HAL_GPIO_DeInit( GPIOC, GPIO_PIN_1 | GPIO_PIN_4 | GPIO_PIN_5 );

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
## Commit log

2020-05-18 add dynamic / silence wav file demo
2022-07-25 add firmware
